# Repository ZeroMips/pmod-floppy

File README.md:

# Pmod-Floppy

This is a Kicad board design of a Pmod module for connecting standard PC floppy
drives to a FPGA. 
My main usecase was in teaching myself some FPGA programming using the Nandland
Go board. The software so far can be found [here](https://github.com/ZeroMips/floppy-fun),
I also documented my experience on the [blog](https://zeromips.org/posts/2024-01-08-superpower/).

This design has been production tested with JLCPCB.
Functional testing has also been performed, it works nicely.

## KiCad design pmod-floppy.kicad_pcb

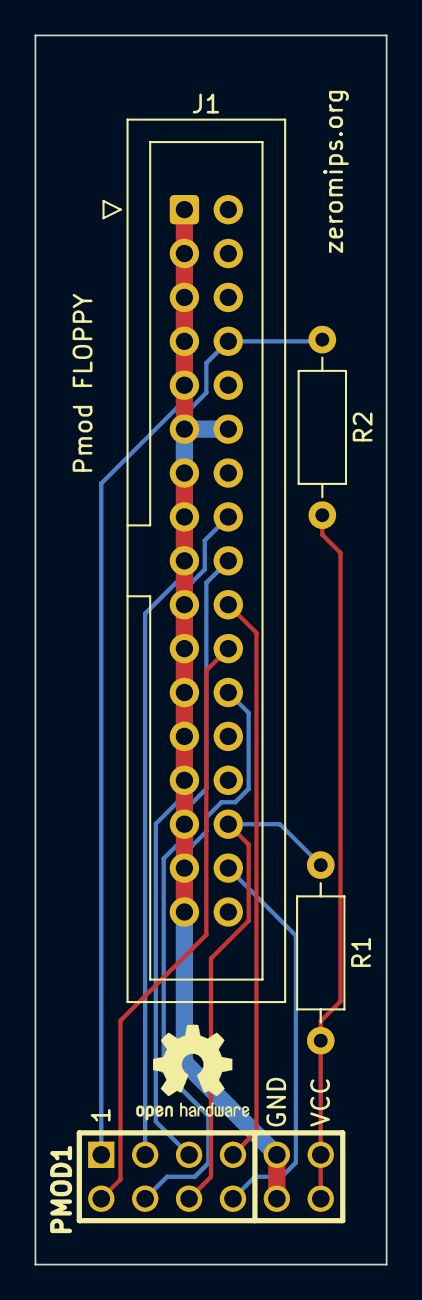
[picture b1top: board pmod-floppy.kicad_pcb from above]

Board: 2 copper layers, 20.3 x 71.1 mm, 4 parts (0 on the bottom side), 10 nets.

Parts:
J1: PC-34 Floppy; IDC-Header_2x17_P2.54mm_Vertical
PMOD1: PMOD-Device-x2-Type-1A-GPIO; pmod_pin_array_6x2
R1, R2: 4k7; R_Axial_DIN0207_L6.3mm_D2.5mm_P10.16mm_Horizontal

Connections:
+3.3V: PMOD1.6 (VCC), PMOD1.12 (VCC), R1.2, R2.2
/Direction Select: J1.18 (Direction_Select), PMOD1.3 (IOA2)
/Index: J1.8 (Index), PMOD1.1 (IOA0), R2.1
/Motor on: J1.16 (Motor_On), PMOD1.2 (IOA1)
/Read Data: J1.30 (Read_Data), PMOD1.9 (IOB2), R1.1
/Side Select: J1.32 (Side_Select), PMOD1.10 (IOB3)
/Step: J1.20 (Step), PMOD1.4 (IOA3)
/Write Data: J1.22 (Write_Data), PMOD1.7 (IOB0)
/Write Gate: J1.24 (Write_Gate), PMOD1.8 (IOB1)
GND: J1.1 (GND), J1.3 (GND), J1.5 (GND), J1.7 (GND), J1.9 (GND), J1.11 (GND), J1.12 (Drive_Select_1), J1.13 (GND), J1.15 (GND), J1.17 (GND), J1.19 (GND), J1.21 (GND), J1.23 (GND), J1.25 (GND), J1.27 (GND), J1.29 (GND), J1.31 (GND), J1.33 (GND), PMOD1.5 (GND), PMOD1.11 (GND)

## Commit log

2024-02-05 Inital commit
2024-02-05 Add LICENSE
